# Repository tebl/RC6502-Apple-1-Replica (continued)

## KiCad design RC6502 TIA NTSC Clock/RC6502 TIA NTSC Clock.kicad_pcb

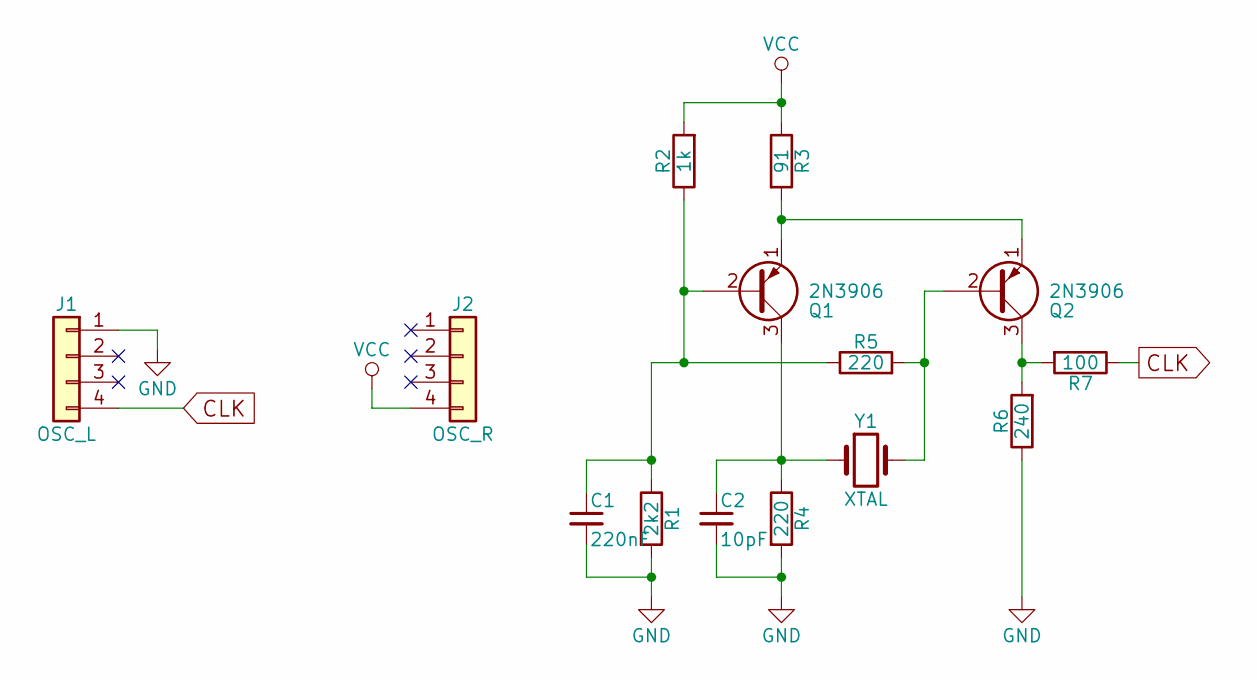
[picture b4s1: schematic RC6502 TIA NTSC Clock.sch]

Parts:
C1: 220nF; C_Disc_D5.0mm_W2.5mm_P5.00mm
C2: 10pF; C_Disc_D5.0mm_W2.5mm_P5.00mm
J1: OSC_L; Pin_Header_Straight_1x04_Pitch2.54mm
J2: OSC_R; Pin_Header_Straight_1x04_Pitch2.54mm
Q1, Q2: 2N3906; TO-92_Inline_Wide
R1: 2k2; R_Axial_DIN0207_L6.3mm_D2.5mm_P10.16mm_Horizontal
R2: 1k; R_Axial_DIN0207_L6.3mm_D2.5mm_P10.16mm_Horizontal
R3: 91; R_Axial_DIN0207_L6.3mm_D2.5mm_P10.16mm_Horizontal
R4, R5: 220; R_Axial_DIN0207_L6.3mm_D2.5mm_P10.16mm_Horizontal
R6: 240; R_Axial_DIN0207_L6.3mm_D2.5mm_P10.16mm_Horizontal
R7: 100; R_Axial_DIN0207_L6.3mm_D2.5mm_P10.16mm_Horizontal
Y1: XTAL; Crystal_HC49-U_Vertical

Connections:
CLK: J1.4, R7.1
GND: C1.2, C2.2, J1.1, R1.2, R4.2, R6.1
unnamed: C1.1, Q1.2 (B), R1.1, R2.1, R5.1
unnamed: C2.1, Q1.3 (C), R4.1, Y1.1
unnamed: Q1.1 (E), Q2.1 (E), R3.2
unnamed: Q2.2 (B), R5.2, Y1.2
unnamed: Q2.3 (C), R6.2, R7.2
VCC: J2.4, R2.2, R3.1

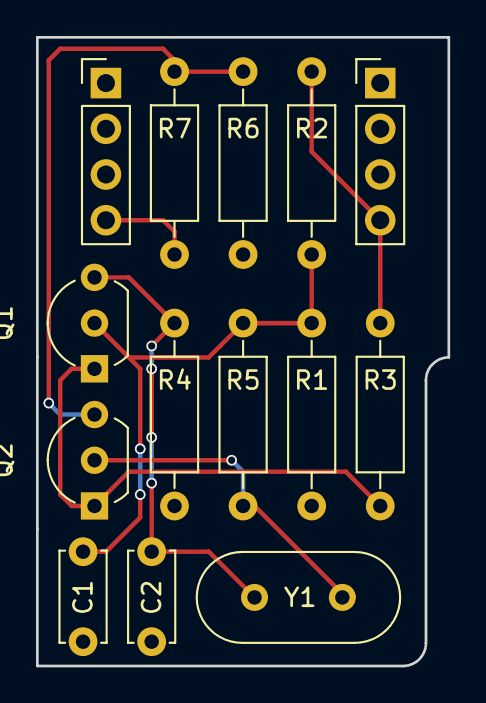
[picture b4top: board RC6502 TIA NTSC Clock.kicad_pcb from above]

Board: 2 copper layers, 22.9 x 34.9 mm, 14 parts (0 on the bottom side), 8 nets.

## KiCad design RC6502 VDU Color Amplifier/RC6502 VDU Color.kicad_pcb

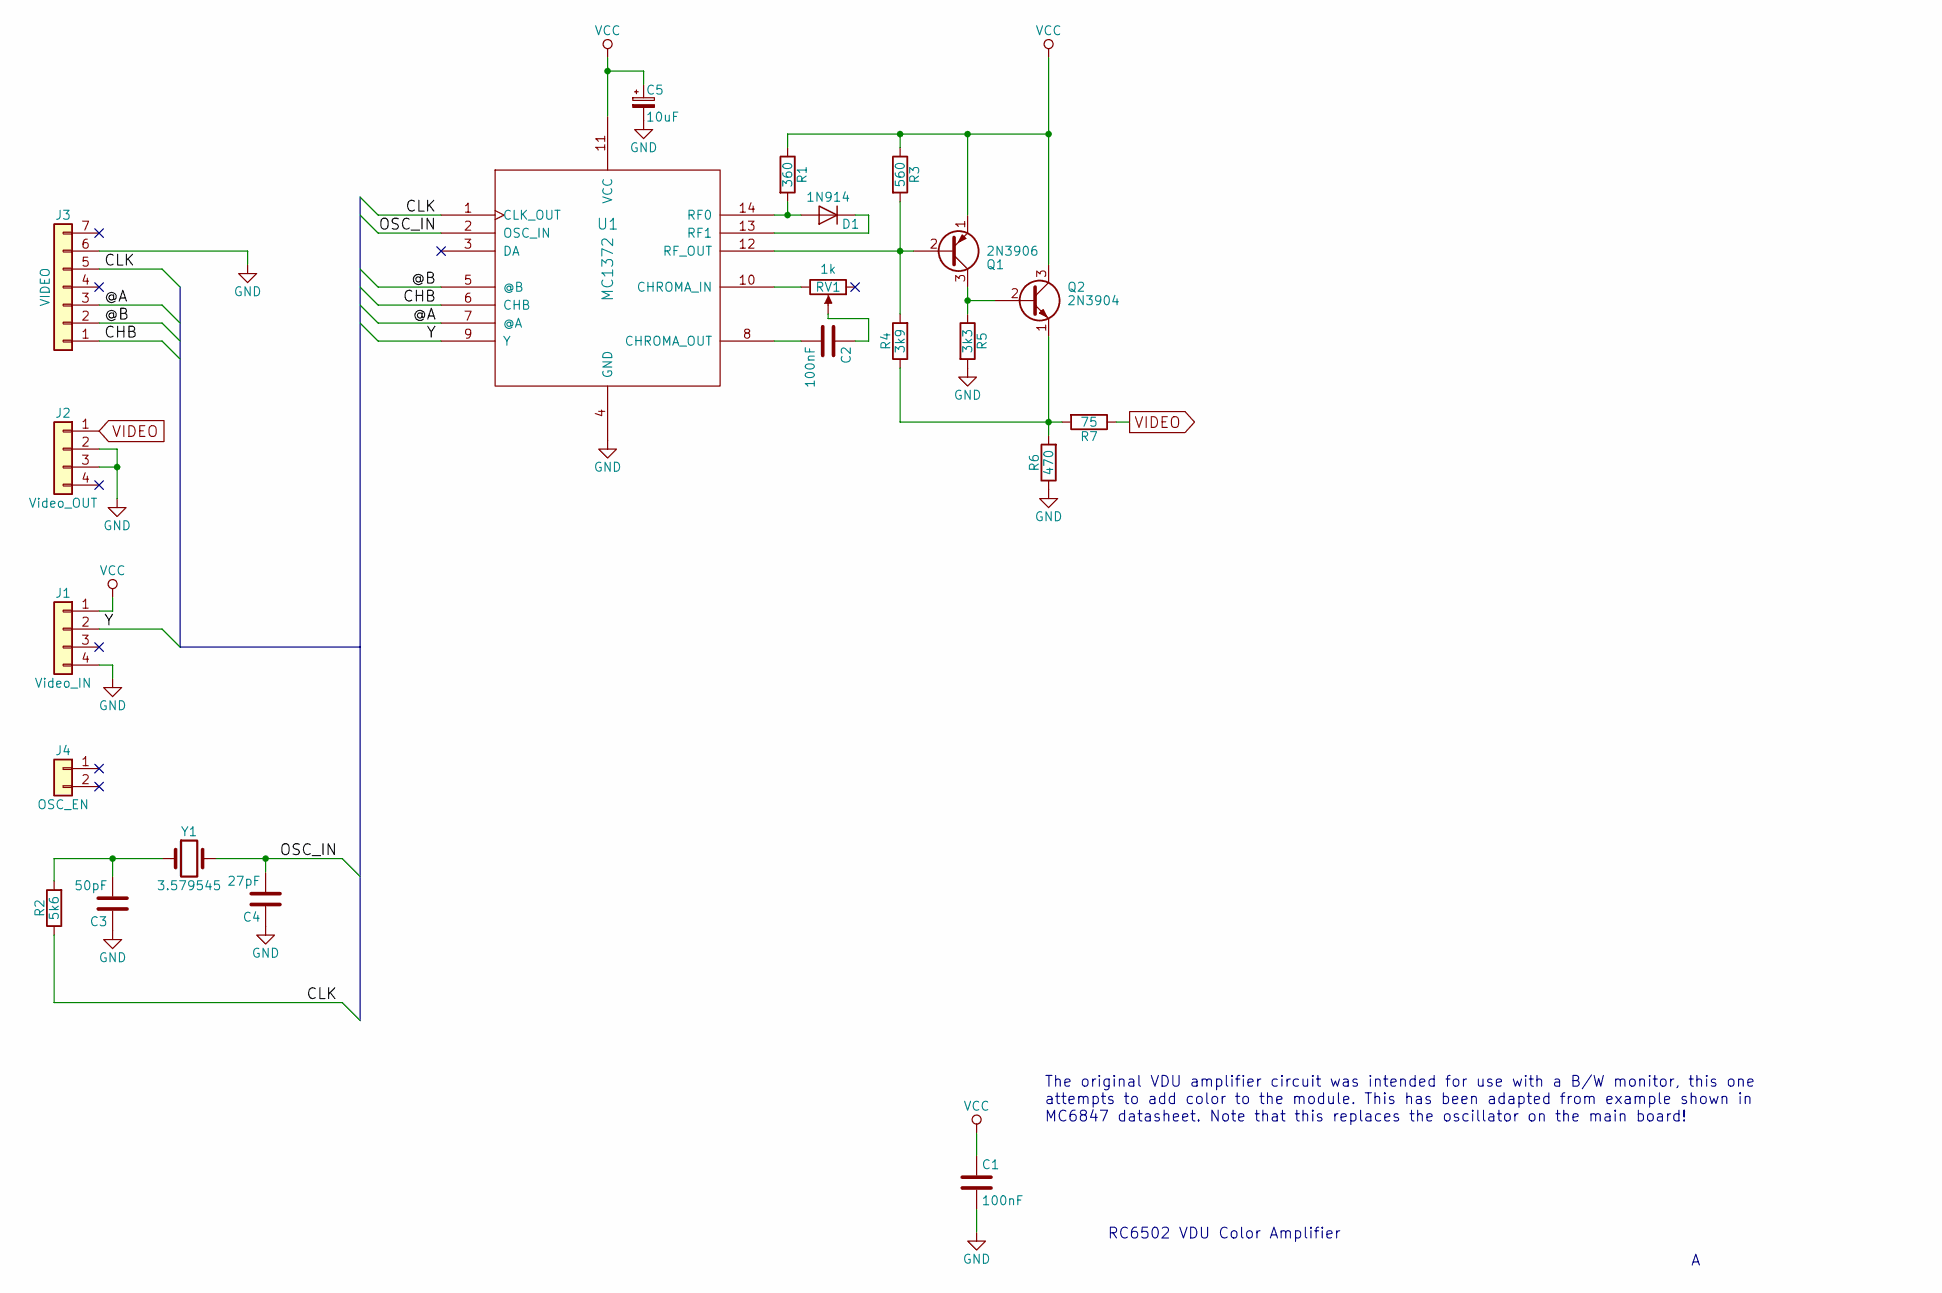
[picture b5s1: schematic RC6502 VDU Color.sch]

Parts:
C1, C2: 100nF; C_Disc_D4.7mm_W2.5mm_P5.00mm
C3: 50pF; C_Disc_D4.7mm_W2.5mm_P5.00mm
C4: 27pF; C_Disc_D4.7mm_W2.5mm_P5.00mm
C5: 10uF; CP_Radial_D4.0mm_P2.00mm
D1: 1N914; D_DO-35_SOD27_P7.62mm_Horizontal
J1: Video_IN; Pin_Header_Straight_1x04_Pitch2.54mm
J2: Video_OUT; Pin_Header_Straight_1x04_Pitch2.54mm
J3: VIDEO; Pin_Header_Straight_1x07_Pitch2.54mm
J4: OSC_EN; Pin_Header_Straight_1x02_Pitch2.54mm
Q1: 2N3906; TO-92_Inline_Wide
Q2: 2N3904; TO-92_Inline_Wide
R1: 360; R_Axial_DIN0207_L6.3mm_D2.5mm_P10.16mm_Horizontal
R2: 5k6; R_Axial_DIN0207_L6.3mm_D2.5mm_P10.16mm_Horizontal
R3: 560; R_Axial_DIN0207_L6.3mm_D2.5mm_P10.16mm_Horizontal
R4: 3k9; R_Axial_DIN0207_L6.3mm_D2.5mm_P10.16mm_Horizontal
R5: 3k3; R_Axial_DIN0207_L6.3mm_D2.5mm_P10.16mm_Horizontal
R6: 470; R_Axial_DIN0207_L6.3mm_D2.5mm_P10.16mm_Horizontal
R7: 75; R_Axial_DIN0207_L6.3mm_D2.5mm_P10.16mm_Horizontal
RV1: 1k; Potentiometer_Trimmer_Bourns_3296W
U1: MC1372; DIP-14_W7.62mm_Socket
Y1: 3.579545; Crystal_HC49-U_Vertical

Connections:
/@A: J3.3, U1.7 (@A)
/@B: J3.2, U1.5 (@B)
/CHB: J3.1, U1.6 (CHB)
/CLK: J3.5, R2.1, U1.1 (CLK_OUT)
/OSC_IN: C4.2, U1.2 (OSC_IN), Y1.2
/Y: J1.2, U1.9 (Y)
GND: C1.2, C3.1, C4.1, C5.2, J1.4, J2.2, J2.3, J3.6, R5.2, R6.1, U1.4 (GND)
unnamed: C2.1, RV1.2
unnamed: C2.2, U1.8 (CHROMA_OUT)
unnamed: C3.2, R2.2, Y1.1
unnamed: D1.1 (K), U1.13 (RF1)
unnamed: D1.2 (A), R1.2, U1.14 (RF0)
unnamed: Q1.2 (B), R3.2, R4.2, U1.12 (RF_OUT)
unnamed: Q1.3 (C), Q2.2 (B), R5.1
unnamed: Q2.1 (E), R4.1, R6.2, R7.2
unnamed: RV1.3, U1.10 (CHROMA_IN)
VCC: C1.1, C5.1, J1.1, Q1.1 (E), Q2.3 (C), R1.1, R3.1, U1.11 (VCC)
VIDEO: J2.1, R7.1

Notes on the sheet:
RC6502 VDU Color Amplifier
The original VDU amplifier circuit was intended for use with a B/W monitor, this one attempts to add color to the module. This has been adapted from example shown in MC6847 datasheet. Note that this replaces the oscillator on the main board!

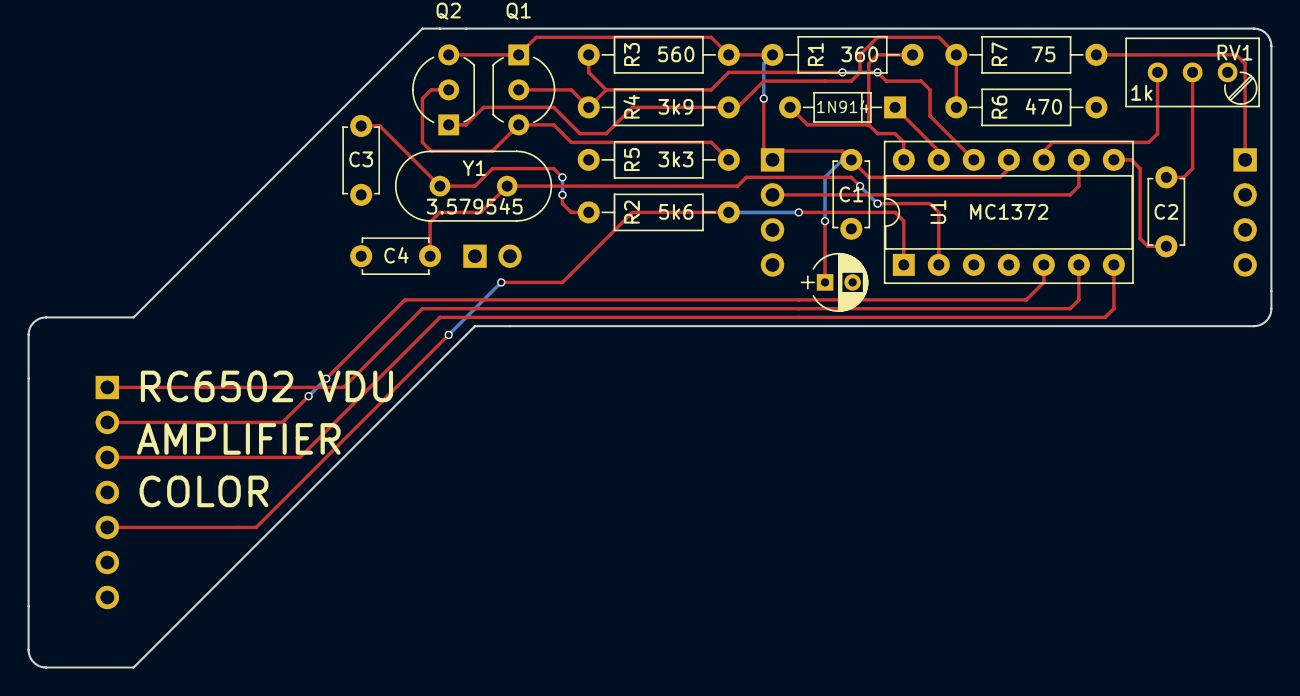
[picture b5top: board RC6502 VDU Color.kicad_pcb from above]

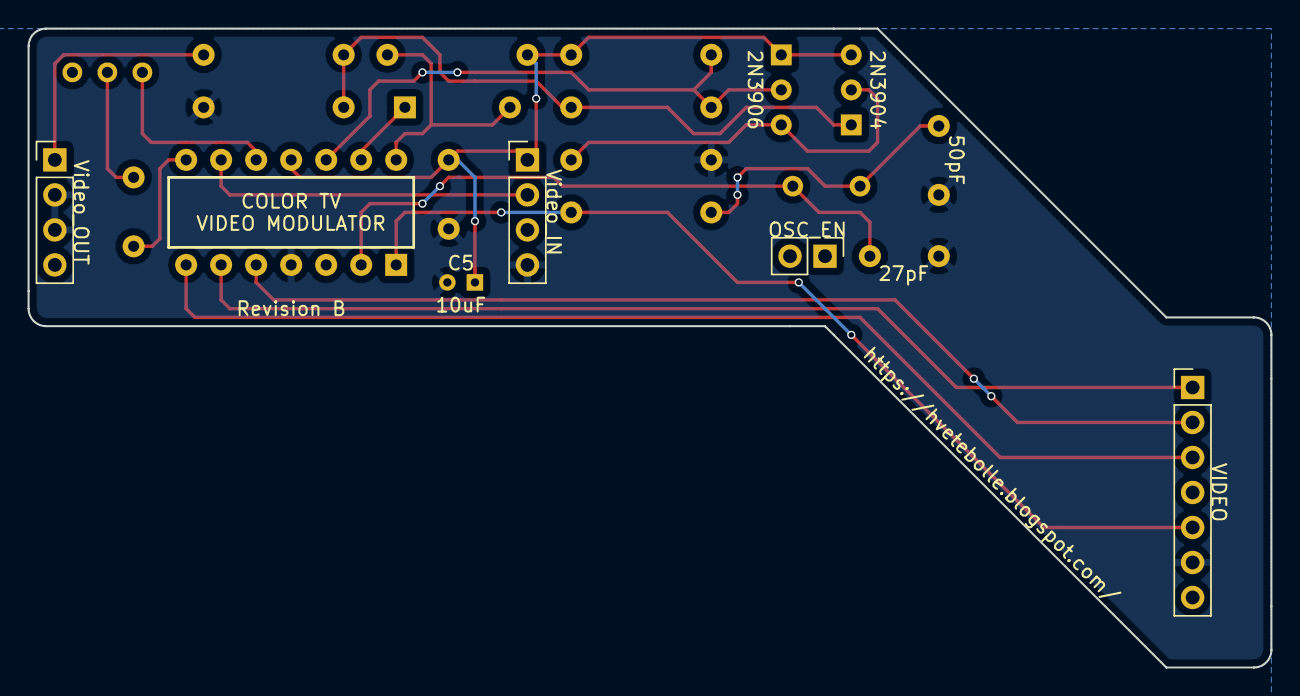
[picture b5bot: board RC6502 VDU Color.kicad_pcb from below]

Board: 2 copper layers, 90.2 x 46.4 mm, 22 parts (4 on the bottom side), 18 nets.

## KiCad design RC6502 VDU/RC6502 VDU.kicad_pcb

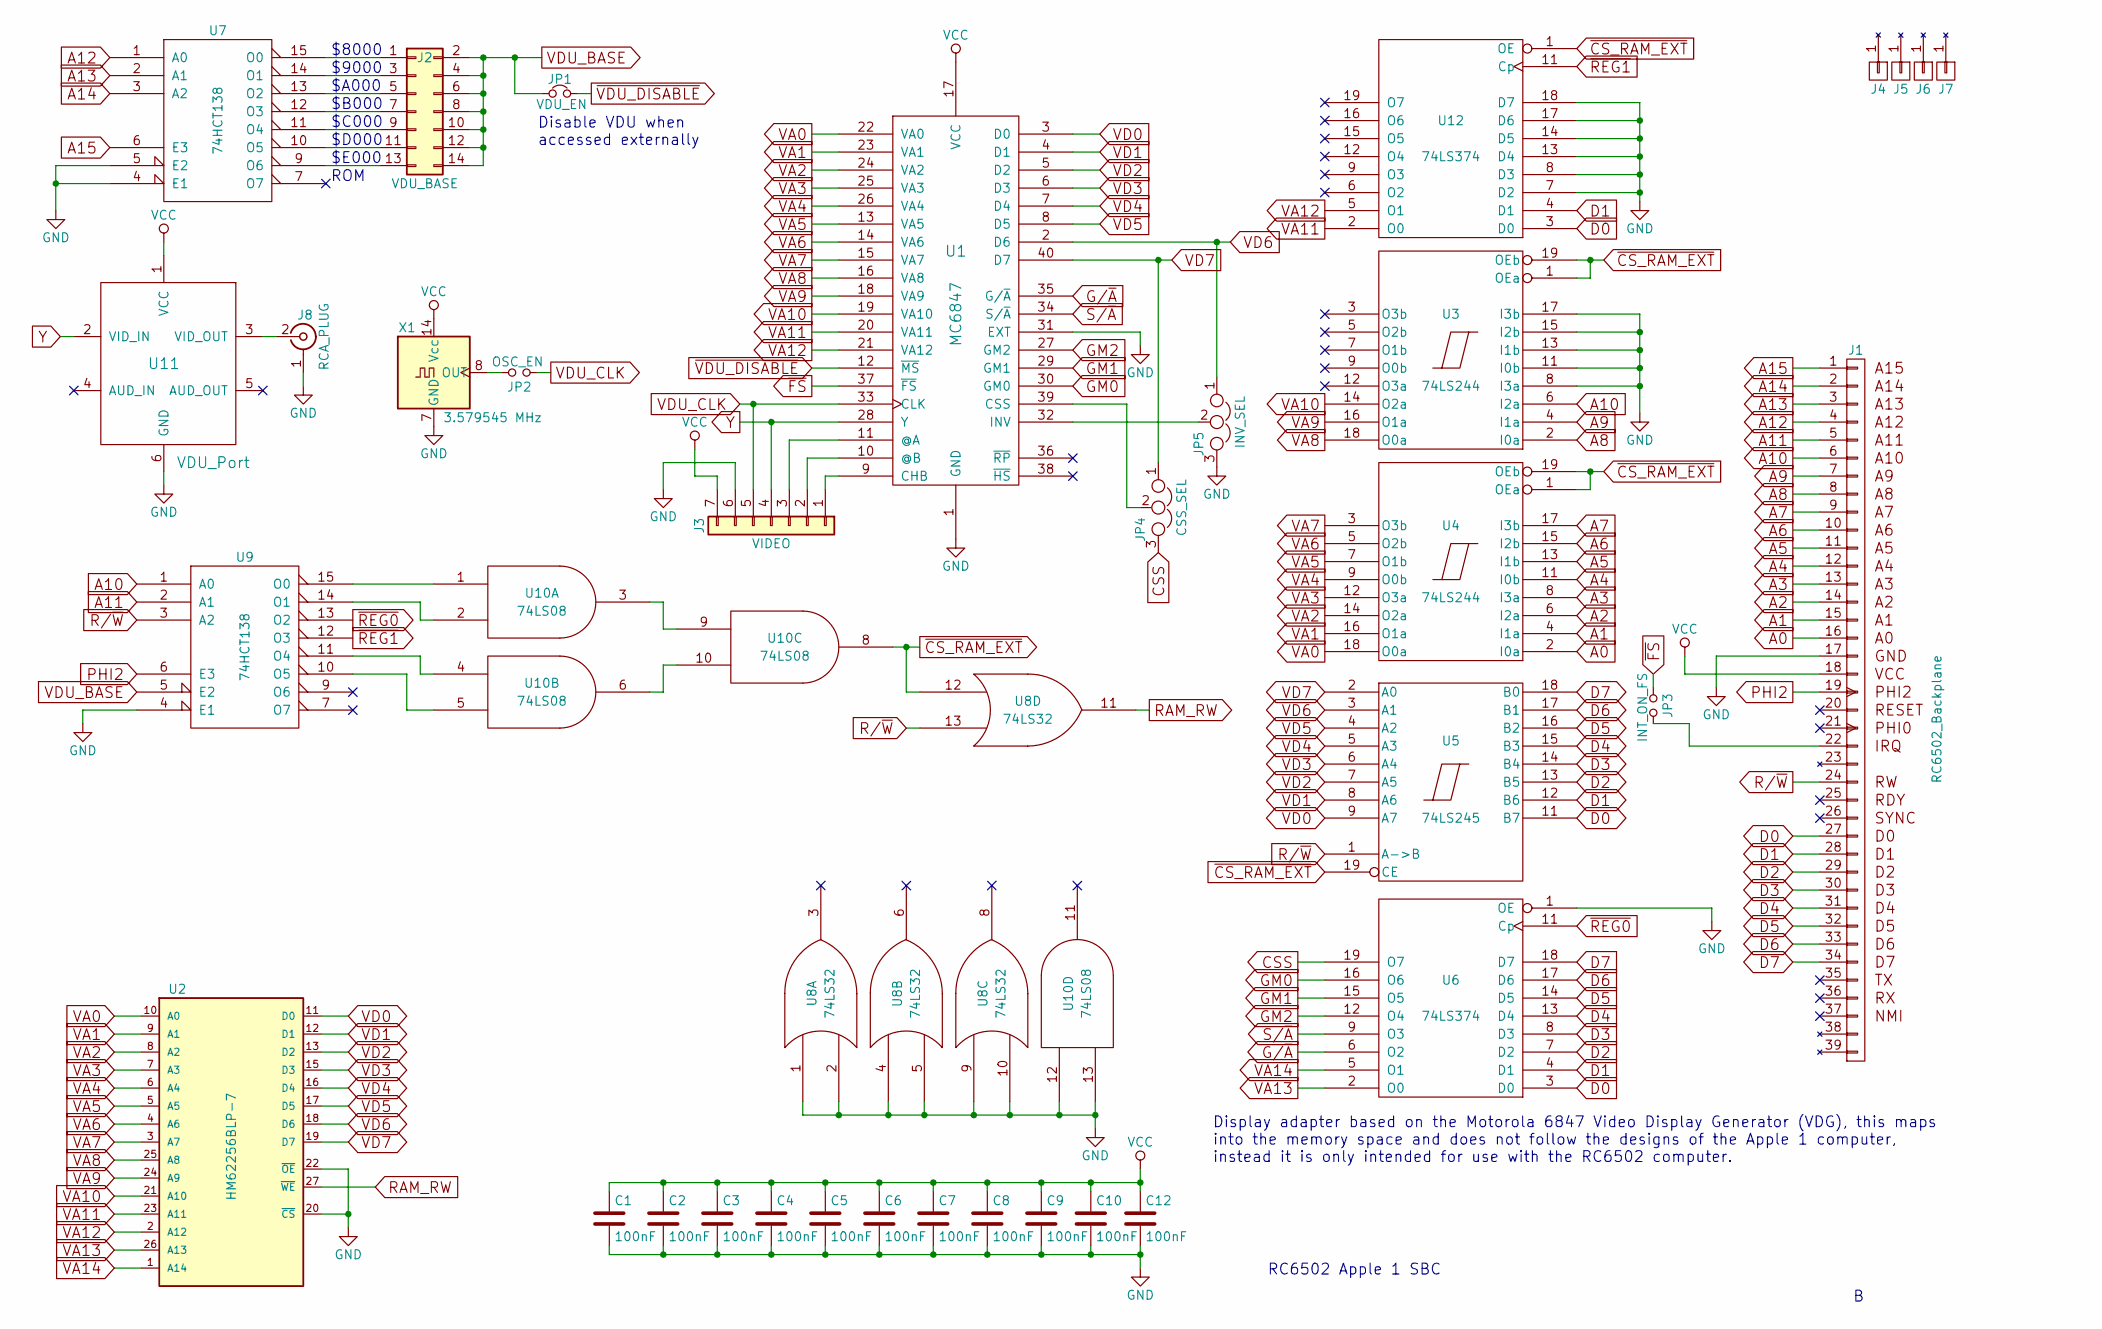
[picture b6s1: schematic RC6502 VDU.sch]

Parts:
C1, C2, C3, C4, C5, C6, C7, C8, C9, C10, C12: 100nF; C_Disc_D4.7mm_W2.5mm_P5.00mm
J1: RC6502_Backplane; Pin_Header_Angled_1x39_Pitch2.54mm
J2: VDU_BASE; Pin_Header_Straight_2x07_Pitch2.54mm
J3: VIDEO; Pin_Header_Straight_1x07_Pitch2.54mm
J4, J5, J6, J7: Hole; Mounting
J8: RCA_PLUG; rca_yellow
JP1: VDU_EN; Pin_Header_Straight_1x02_Pitch2.54mm
JP2: OSC_EN; Pin_Header_Straight_1x02_Pitch2.54mm
JP3: INT_ON_FS; Pin_Header_Straight_1x02_Pitch2.54mm
JP4: CSS_SEL; Pin_Header_Straight_1x03_Pitch2.54mm
JP5: INV_SEL; Pin_Header_Straight_1x03_Pitch2.54mm
U1: MC6847; DIP-40_W15.24mm_Socket
U2: HM62256BLP-7; DIP-28_W15.24mm_Socket
U3, U4: 74LS244; DIP-20_W7.62mm_Socket
U5: 74LS245; DIP-20_W7.62mm_Socket
U6, U12: 74LS374; DIP-20_W7.62mm_Socket
U7, U9: 74HCT138; DIP-16_W7.62mm_Socket
U8: 74LS32; DIP-14_W7.62mm_Socket
U10: 74LS08; DIP-14_W7.62mm_Socket
U11: VDU_Port; Amplifier
X1: 3.579545 MHz; Oscillator_DIP-14

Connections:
A0: J1.16 (A0), U4.2 (I0a)
A1: J1.15 (A1), U4.4 (I1a)
A2: J1.14 (A2), U4.6 (I2a)
A3: J1.13 (A3), U4.8 (I3a)
A4: J1.12 (A4), U4.11 (I0b)
A5: J1.11 (A5), U4.13 (I1b)
A6: J1.10 (A6), U4.15 (I2b)
A7: J1.9 (A7), U4.17 (I3b)
A8: J1.8 (A8), U3.2 (I0a)
A9: J1.7 (A9), U3.4 (I1a)
A10: J1.6 (A10), U3.6 (I2a), U9.1 (A0)
A11: J1.5 (A11), U9.2 (A1)
A12: J1.4 (A12), U7.1 (A0)
A13: J1.3 (A13), U7.2 (A1)
A14: J1.2 (A14), U7.3 (A2)
A15: J1.1 (A15), U7.6 (E3)
CSS: JP4.3, U6.19 (O7)
D0: J1.27 (D0), U5.11 (B7), U6.3 (D0), U12.3 (D0)
D1: J1.28 (D1), U5.12 (B6), U6.4 (D1), U12.4 (D1)
D2: J1.29 (D2), U5.13 (B5), U6.7 (D2)
D3: J1.30 (D3), U5.14 (B4), U6.8 (D3)
D4: J1.31 (D4), U5.15 (B3), U6.13 (D4)
D5: J1.32 (D5), U5.16 (B2), U6.14 (D5)
D6: J1.33 (D6), U5.17 (B1), U6.17 (D6)
D7: J1.34 (D7), U5.18 (B0), U6.18 (D7)
G/~A: U1.35 (G/~A), U6.6 (O2)
GM0: U1.30 (GM0), U6.16 (O6)
GM1: U1.29 (GM1), U6.15 (O5)
GM2: U1.27 (GM2), U6.12 (O4)
GND: C1.2, C2.2, C3.2, C4.2, C5.2, C6.2, C7.2, C8.2, C9.2, C10.2, C12.2, J1.17, J3.6, J8.1 (Ext), JP5.3, U1.1 (GND), U1.31 (EXT), U2.14 (GND), U2.20 (~CS), U2.22 (~OE), U3.8 (I3a), U3.10 (GND), U3.11 (I0b), U3.13 (I1b), U3.15 (I2b), U3.17 (I3b), U4.10 (GND), U5.10 (GND), U6.1 (OE), U6.10 (GND), U7.4 (E1), U7.5 (E2), U7.8 (GND), U8.1, U8.2, U8.4, U8.5, U8.7 (GND), U8.9, U8.10, U9.4 (E1), U9.8 (GND), U10.7 (GND), U10.12, U10.13, U11.6 (GND), U12.7 (D2), U12.8 (D3), U12.10 (GND), U12.13 (D4), U12.14 (D5), U12.17 (D6), U12.18 (D7), X1.7 (GND)
unnamed: J1.22 (IRQ), JP3.2
unnamed: J2.1, U7.15 (O0)
unnamed: J2.3, U7.14 (O1)
unnamed: J2.5, U7.13 (O2)
unnamed: J2.7, U7.12 (O3)
unnamed: J2.9, U7.11 (O4)
unnamed: J2.11, U7.10 (O5)
unnamed: J2.13, U7.9 (O6)
unnamed: J3.1, U1.9 (CHB)
unnamed: J3.2, U1.10 (@B)
unnamed: J3.3, U1.11 (@A)
unnamed: J8.2 (In), U11.3 (VID_OUT)
unnamed: JP2.2, X1.8 (OUT)
unnamed: JP4.2, U1.39 (CSS)
unnamed: JP5.2, U1.32 (INV)
unnamed: U9.15 (O0), U10.1
unnamed: U9.14 (O1), U10.2
unnamed: U10.3, U10.9
unnamed: U9.11 (O4), U10.4
unnamed: U9.10 (O5), U10.5
unnamed: U10.6, U10.10
PHI2: J1.19 (PHI2), U9.6 (E3)
R/~W: J1.24 (RW), U5.1 (A->B), U8.13, U9.3 (A2)
RAM_RW: U2.27 (~WE), U8.11
S/~A: U1.34 (S/~A), U6.9 (O3)
VA0: U1.22 (VA0), U2.10 (A0), U4.18 (O0a)
VA1: U1.23 (VA1), U2.9 (A1), U4.16 (O1a)
VA2: U1.24 (VA2), U2.8 (A2), U4.14 (O2a)
VA3: U1.25 (VA3), U2.7 (A3), U4.12 (O3a)
VA4: U1.26 (VA4), U2.6 (A4), U4.9 (O0b)
VA5: U1.13 (VA5), U2.5 (A5), U4.7 (O1b)
VA6: U1.14 (VA6), U2.4 (A6), U4.5 (O2b)
VA7: U1.15 (VA7), U2.3 (A7), U4.3 (O3b)
VA8: U1.16 (VA8), U2.25 (A8), U3.18 (O0a)
VA9: U1.18 (VA9), U2.24 (A9), U3.16 (O1a)
VA10: U1.19 (VA10), U2.21 (A10), U3.14 (O2a)
VA11: U1.20 (VA11), U2.23 (A11), U12.2 (O0)
VA12: U1.21 (VA12), U2.2 (A12), U12.5 (O1)
VA13: U2.26 (A13), U6.2 (O0)
VA14: U2.1 (A14), U6.5 (O1)
VCC: C1.1, C2.1, C3.1, C4.1, C5.1, C6.1, C7.1, C8.1, C9.1, C10.1, C12.1, J1.18, J3.7, U1.17 (VCC), U2.28 (VCC), U3.20 (VCC), U4.20 (VCC), U5.20 (VCC), U6.20 (VCC), U7.16 (VCC), U8.14 (VCC), U9.16 (VCC), U10.14 (VCC), U11.1 (VCC), U12.20 (VCC), X1.14 (Vcc)
VD0: U1.3 (D0), U2.11 (D0), U5.9 (A7)
VD1: U1.4 (D1), U2.12 (D1), U5.8 (A6)
VD2: U1.5 (D2), U2.13 (D2), U5.7 (A5)
VD3: U1.6 (D3), U2.15 (D3), U5.6 (A4)
VD4: U1.7 (D4), U2.16 (D4), U5.5 (A3)
VD5: U1.8 (D5), U2.17 (D5), U5.4 (A2)
VD6: JP5.1, U1.2 (D6), U2.18 (D6), U5.3 (A1)
VD7: JP4.1, U1.40 (D7), U2.19 (D7), U5.2 (A0)
VDU_BASE: J2.2, J2.4, J2.6, J2.8, J2.10, J2.12, J2.14, JP1.1, U9.5 (E2)
VDU_CLK: J3.5, JP2.1, U1.33 (CLK)
Y: J3.4, U1.28 (Y), U11.2 (VID_IN)
~CS_RAM_EXT: U3.1 (OEa), U3.19 (OEb), U4.1 (OEa), U4.19 (OEb), U5.19 (CE), U8.12, U10.8, U12.1 (OE)
~FS: JP3.1, U1.37 (~FS)
~REG0: U6.11 (Cp), U9.13 (O2)
~REG1: U9.12 (O3), U12.11 (Cp)
~VDU_DISABLE: JP1.2, U1.12 (~MS)

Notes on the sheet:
RC6502 Apple 1 SBC
ROM
$C000
$B000
$A000
$9000
$8000
Disable VDU when accessed externally
Display adapter based on the Motorola 6847 Video Display Generator (VDG), this maps into the memory space and does not follow the designs of the Apple 1 computer, instead it is only intended for use with the RC6502 computer.
$D000
$E000

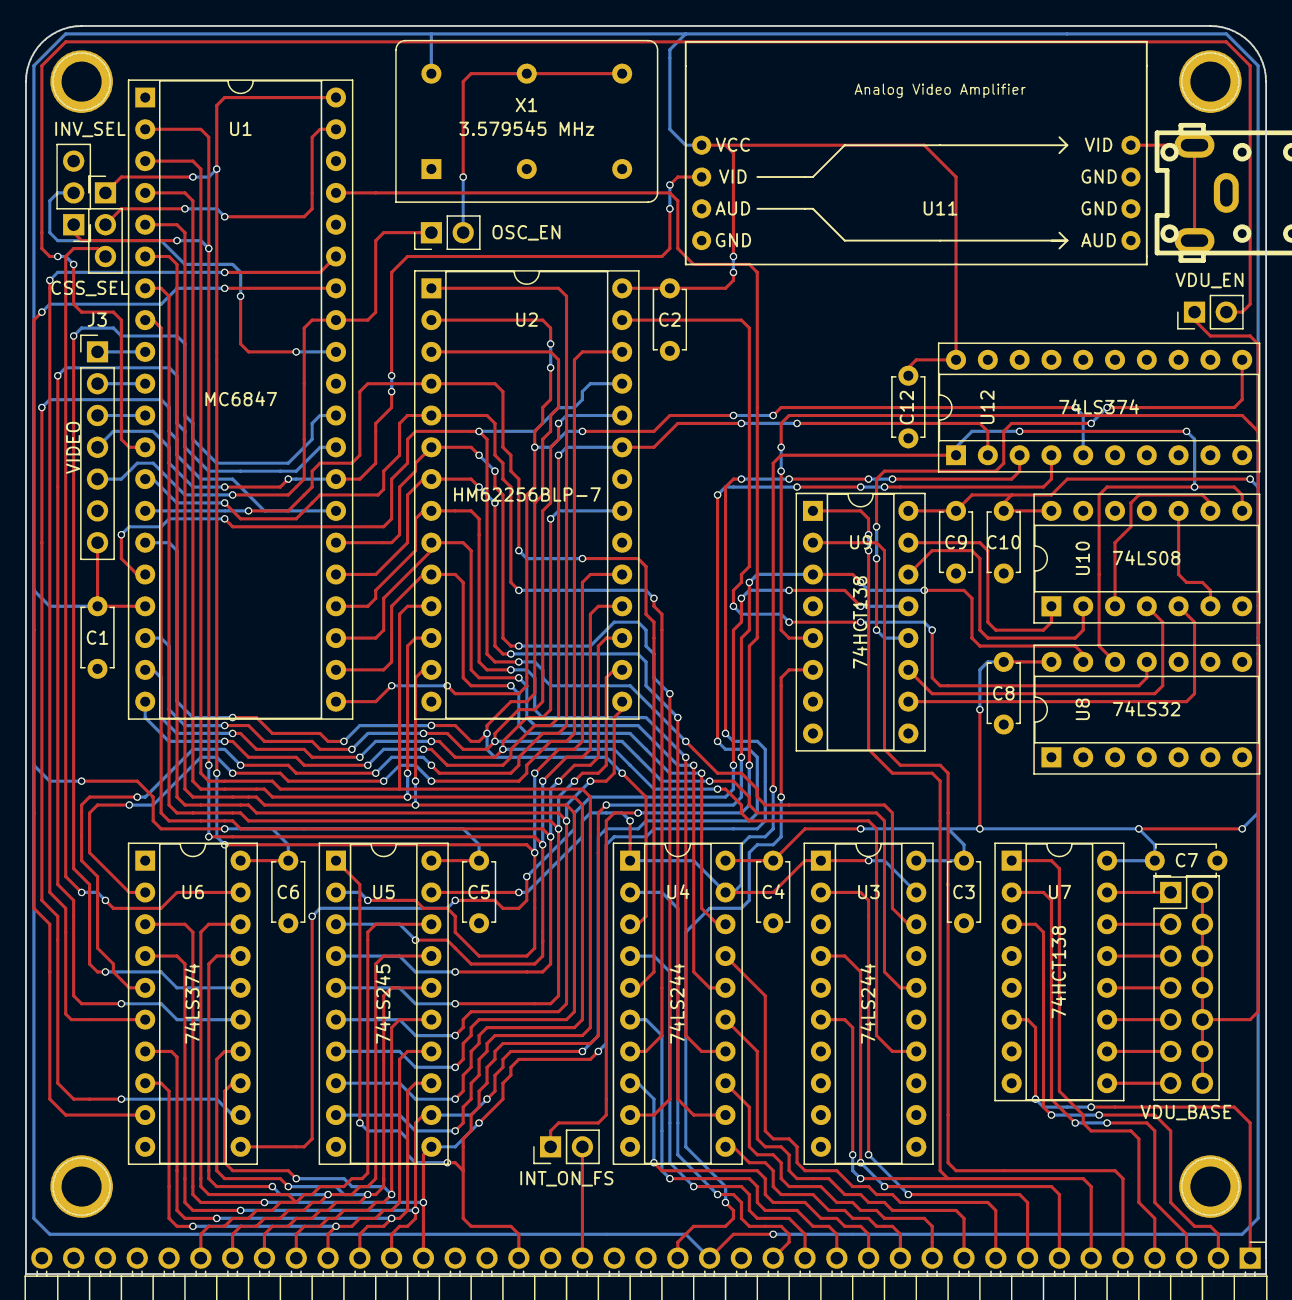
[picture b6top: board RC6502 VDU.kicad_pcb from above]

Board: 2 copper layers, 99.1 x 99.7 mm, 37 parts (0 on the bottom side), 87 nets.

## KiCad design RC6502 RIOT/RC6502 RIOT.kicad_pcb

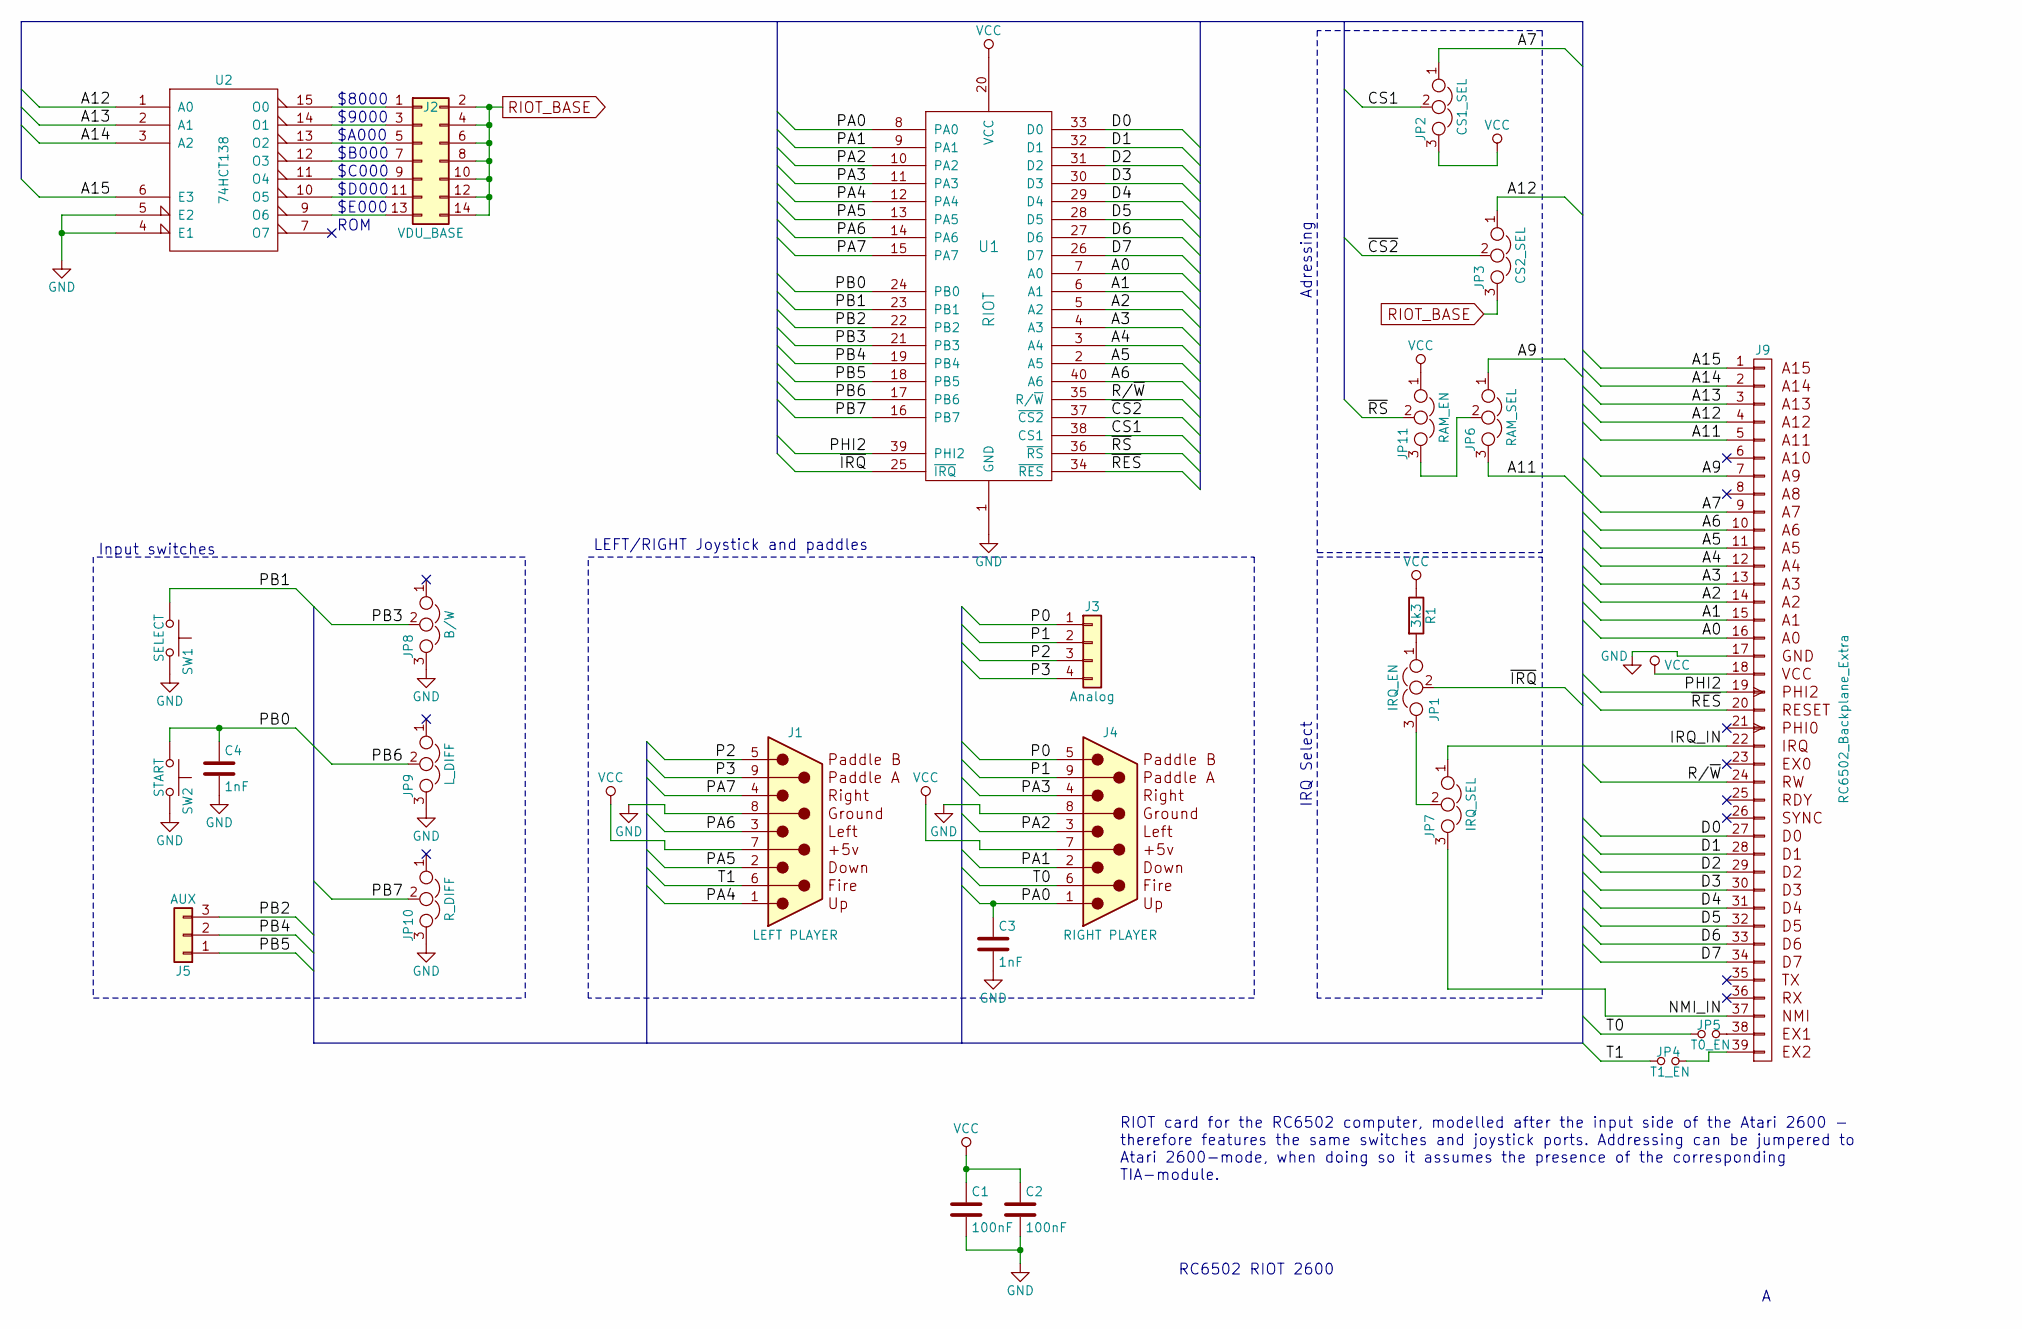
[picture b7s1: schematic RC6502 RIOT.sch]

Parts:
C1, C2: 100nF; C_Disc_D4.7mm_W2.5mm_P5.00mm
C3, C4: 1nF; C_Disc_D4.7mm_W2.5mm_P5.00mm
J1: LEFT PLAYER; DSUB-9_Male_Vertical_Pitch2.77x2.84mm
J2: VDU_BASE; Pin_Header_Straight_2x07_Pitch2.54mm
J3: Analog; Pin_Header_Straight_1x04_Pitch2.54mm
J4: RIGHT PLAYER; DSUB-9_Male_Vertical_Pitch2.77x2.84mm
J5: AUX; Pin_Header_Straight_1x03_Pitch2.54mm
J9: RC6502_Backplane_Extra; Pin_Header_Angled_1x39_Pitch2.54mm
JP1: IRQ_EN; Pin_Header_Straight_1x03_Pitch2.54mm
JP2: CS1_SEL; Pin_Header_Straight_1x03_Pitch2.54mm
JP3: CS2_SEL; Pin_Header_Straight_1x03_Pitch2.54mm
JP4: T1_EN; Pin_Header_Straight_1x02_Pitch2.54mm
JP5: T0_EN; Pin_Header_Straight_1x02_Pitch2.54mm
JP6: RAM_SEL; Pin_Header_Straight_1x03_Pitch2.54mm
JP7: IRQ_SEL; Pin_Header_Straight_1x03_Pitch2.54mm
JP8: B/W; Pin_Header_Straight_1x03_Pitch2.54mm
JP9: L_DIFF; Pin_Header_Straight_1x03_Pitch2.54mm
JP10: R_DIFF; Pin_Header_Straight_1x03_Pitch2.54mm
JP11: RAM_EN; Pin_Header_Straight_1x03_Pitch2.54mm
R1: 3k3; R_Axial_DIN0207_L6.3mm_D2.5mm_P10.16mm_Horizontal
SW1: SELECT; SW_PUSH_6mm
SW2: START; SW_PUSH_6mm
U1: RIOT; DIP-40_W15.24mm_Socket
U2: 74HCT138; DIP-16_W7.62mm_Socket

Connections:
/A0: J9.16 (A0), U1.7 (A0)
/A1: J9.15 (A1), U1.6 (A1)
/A2: J9.14 (A2), U1.5 (A2)
/A3: J9.13 (A3), U1.4 (A3)
/A4: J9.12 (A4), U1.3 (A4)
/A5: J9.11 (A5), U1.2 (A5)
/A6: J9.10 (A6), U1.40 (A6)
/A7: J9.9 (A7), JP2.1
/A9: J9.7 (A9), JP6.1
/A11: J9.5 (A11), JP6.3
/A12: J9.4 (A12), JP3.1, U2.1 (A0)
/A13: J9.3 (A13), U2.2 (A1)
/A14: J9.2 (A14), U2.3 (A2)
/A15: J9.1 (A15), U2.6 (E3)
/CS1: JP2.2, U1.38 (CS1)
/D0: J9.27 (D0), U1.33 (D0)
/D1: J9.28 (D1), U1.32 (D1)
/D2: J9.29 (D2), U1.31 (D2)
/D3: J9.30 (D3), U1.30 (D3)
/D4: J9.31 (D4), U1.29 (D4)
/D5: J9.32 (D5), U1.28 (D5)
/D6: J9.33 (D6), U1.27 (D6)
/D7: J9.34 (D7), U1.26 (D7)
/IRQ_IN: J9.22 (IRQ), JP7.1
/NMI_IN: J9.37 (NMI), JP7.3
/P0: J3.1, J4.5
/P1: J3.2, J4.9
/P2: J1.5, J3.3
/P3: J1.9, J3.4
/PA0: C3.1, J4.1, U1.8 (PA0)
/PA1: J4.2, U1.9 (PA1)
/PA2: J4.3, U1.10 (PA2)
/PA3: J4.4, U1.11 (PA3)
/PA4: J1.1, U1.12 (PA4)
/PA5: J1.2, U1.13 (PA5)
/PA6: J1.3, U1.14 (PA6)
/PA7: J1.4, U1.15 (PA7)
/PB0: C4.1, SW2.1, U1.24 (PB0)
/PB1: SW1.1, U1.23 (PB1)
/PB2: J5.3, U1.22 (PB2)
/PB3: JP8.2, U1.21 (PB3)
/PB4: J5.2, U1.19 (PB4)
/PB5: J5.1, U1.18 (PB5)
/PB6: JP9.2, U1.17 (PB6)
/PB7: JP10.2, U1.16 (PB7)
/PHI2: J9.19 (PHI2), U1.39 (PHI2)
/R/~W: J9.24 (RW), U1.35 (R/~W)
/T0: J4.6, JP5.1
/T1: J1.6, JP4.1
/~CS2: JP3.2, U1.37 (~CS2)
/~IRQ: JP1.2, U1.25 (~IRQ)
/~RES: J9.20 (RESET), U1.34 (~RES)
/~RS: JP11.2, U1.36 (~RS)
GND: C1.2, C2.2, C3.2, C4.2, J1.8, J4.8, J9.17, JP8.3, JP9.3, JP10.3, SW1.2, SW2.2, U1.1 (GND), U2.4 (E1), U2.5 (E2), U2.8 (GND)
unnamed: J2.1, U2.15 (O0)
unnamed: J2.3, U2.14 (O1)
unnamed: J2.5, U2.13 (O2)
unnamed: J2.7, U2.12 (O3)
unnamed: J2.9, U2.11 (O4)
unnamed: J2.11, U2.10 (O5)
unnamed: J2.13, U2.9 (O6)
unnamed: J9.38 (EX1), JP5.2
unnamed: J9.39 (EX2), JP4.2
unnamed: JP1.1, R1.2
unnamed: JP1.3, JP7.2
unnamed: JP6.2, JP11.3
RIOT_BASE: J2.2, J2.4, J2.6, J2.8, J2.10, J2.12, J2.14, JP3.3
VCC: C1.1, C2.1, J1.7, J4.7, J9.18, JP2.3, JP11.1, R1.1, U1.20 (VCC), U2.16 (VCC)

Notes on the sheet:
RC6502 RIOT 2600
ROM
$C000
$B000
$A000
$9000
$8000
$D000
$E000
Adressing
IRQ Select
LEFT/RIGHT Joystick and paddles
Input switches
RIOT card for the RC6502 computer, modelled after the input side of the Atari 2600 - therefore features the same switches and joystick ports. Addressing can be jumpered to Atari 2600-mode, when doing so it assumes the presence of the corresponding TIA-module.

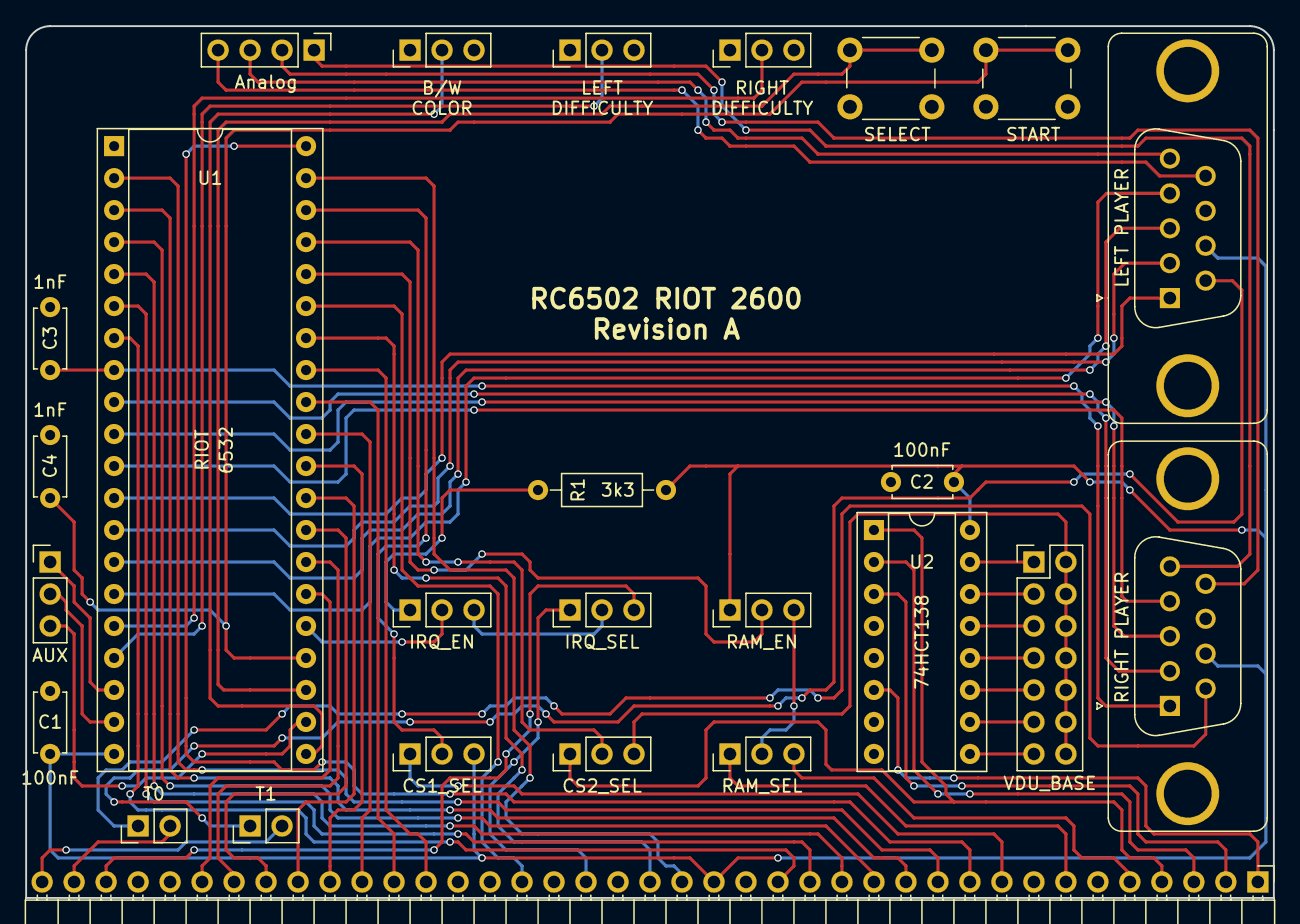
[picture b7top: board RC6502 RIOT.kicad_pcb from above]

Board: 2 copper layers, 99.1 x 69.2 mm, 26 parts (0 on the bottom side), 68 nets.
